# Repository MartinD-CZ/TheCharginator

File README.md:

# The CHARGINATOR
*Upcycle your old ATX power supply into this 11-port QC-compatible charging monstrosity!*

Features:
* connects to an old PC power supply via a 24-pin MOLEX Mini-fit Jr. connector.
* provides power-on switch and LED, stand-by LED and three load resistors.
* 4 USB ports, compatible with QC3.0 (up to 24 W per port, 12 V 2 A), FCP (Huawei), DCP (Apple) and BCP (Battery Charging Protocol).
* 6 USB ports, compatible with DCP and BCP (5 V 2 A per port).
* 1 USB stand-by port, copatible with DCP and BCP (5 V 2 A per port).
* Each output individually fused with resetable fuse.
* Also, screw terminals with 3.3, 5 and 12 V are available.

Links:
* [Hackaday article]()
* [Article on my blog, explaining how the QC part works](http://embedblog.eu/?p=504)
* [FP6601 datasheet](https://datasheet.lcsc.com/szlcsc/Fitipower-Integrated-Tech-FP6601QS6_C86198.pdf)

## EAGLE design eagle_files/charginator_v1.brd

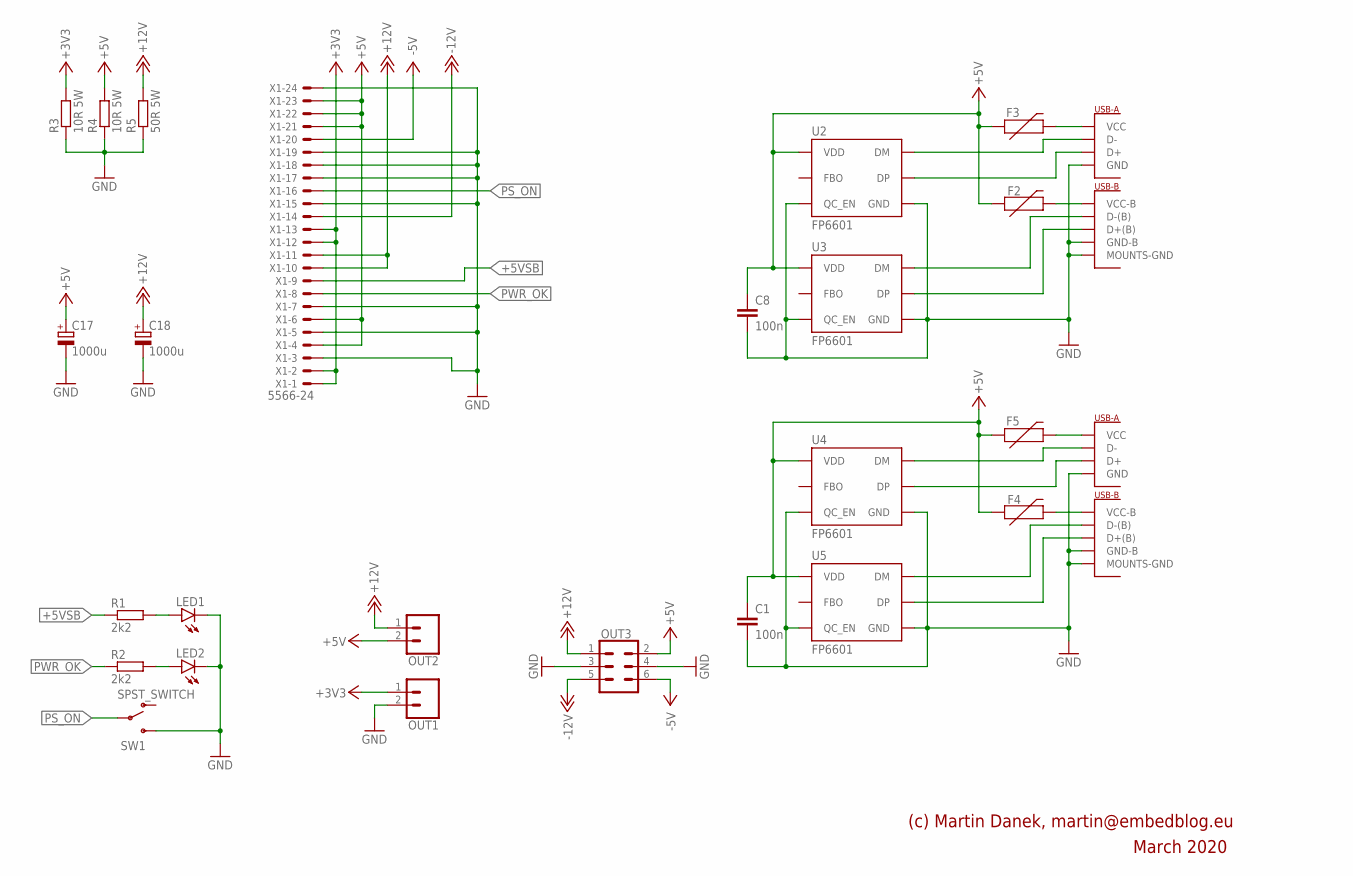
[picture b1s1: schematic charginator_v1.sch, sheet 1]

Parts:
C1, C8: 100n; C1206
C17: 1000u; E5-10,5
C18: 1000u; E5-13
F2, F3, F4, F5: 6V/2A; 1206
LED1, LED2: LED5MM
OUT1, OUT2: 5MM_SCREWTERMINAL_LARGE; SCREWTERMINAL-5MM-2
OUT3: FEMALE 2x3; 2X3
R1, R2: 2k2; M1206
R3, R4: 10R 5W; POWER_RESISTOR_5W
R5: 50R 5W; POWER_RESISTOR_5W
SW1: SPST_SWITCH; TL3XYO
U2, U3, U4, U5: FP6601; SOT23-6
U$1, U$2: DUAL-PORT-USB-REC; DUAL-PORT-USB
X1: 5566-24

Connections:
+3V3: OUT1.1, R3.P$2 (2), X1.1, X1.2, X1.12, X1.13
+5V: C1.1, C8.1, C17.+, F2.1, F3.1, F4.1, F5.1, OUT2.2, OUT3.2, R4.P$2 (2), U2.5 (VDD), U3.5 (VDD), U4.5 (VDD), U5.5 (VDD), X1.4, X1.6, X1.21, X1.22, X1.23; also elsewhere on the board
+5VSB: R1.1, X1.9; also elsewhere on the board
+12V: C18.+, OUT2.1, OUT3.1, R5.P$2 (2), X1.10, X1.11; also elsewhere on the board
-5V: OUT3.6, X1.20
-12V: OUT3.5, X1.14
GND: C1.2, C8.2, C17.-, C18.-, LED1.K (C), LED2.K (C), OUT1.2, OUT3.3, OUT3.4, R3.P$1 (1), R4.P$1 (1), R5.P$1 (1), SW1.1 (S), U2.2 (GND), U2.4 (QC_EN), U3.2 (GND), U3.4 (QC_EN), U4.2 (GND), U4.4 (QC_EN), U5.2 (GND), U5.4 (QC_EN), U$1.GND (MOUNTS-GND), U$1.P$2 (MOUNTS-GND), U$1.P$3 (MOUNTS-GND), U$1.P$4 (MOUNTS-GND), U$1.P$9 (GND-B), U$1.P$11 (GND), U$2.GND (MOUNTS-GND), U$2.P$2 (MOUNTS-GND), U$2.P$3 (MOUNTS-GND), U$2.P$4 (MOUNTS-GND), U$2.P$9 (GND-B), U$2.P$11 (GND), X1.3, X1.5, X1.7, X1.15, X1.17, X1.18, X1.19, X1.24; also elsewhere on the board
unnamed: LED1.A, R1.2
unnamed: LED2.A, R2.2
unnamed: F4.2, U$2.P$10 (VCC-B)
unnamed: F5.2, U$2.P$12 (VCC)
unnamed: F2.2, U$1.P$10 (VCC-B)
unnamed: F3.2, U$1.P$12 (VCC)
unnamed: U2.6 (DM), U$1.P$7 (D-)
unnamed: U2.1 (DP), U$1.P$8 (D+)
unnamed: U4.6 (DM), U$2.P$7 (D-)
unnamed: U4.1 (DP), U$2.P$8 (D+)
unnamed: U5.6 (DM), U$2.P$5 (D-(B))
unnamed: U5.1 (DP), U$2.P$6 (D+(B))
unnamed: U3.6 (DM), U$1.P$5 (D-(B))
unnamed: U3.1 (DP), U$1.P$6 (D+(B))
PS_ON: SW1.2, X1.16
PWR_OK: R2.1, X1.8

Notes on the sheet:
(c) Martin Danek, martin@embedblog.eu
March 2020

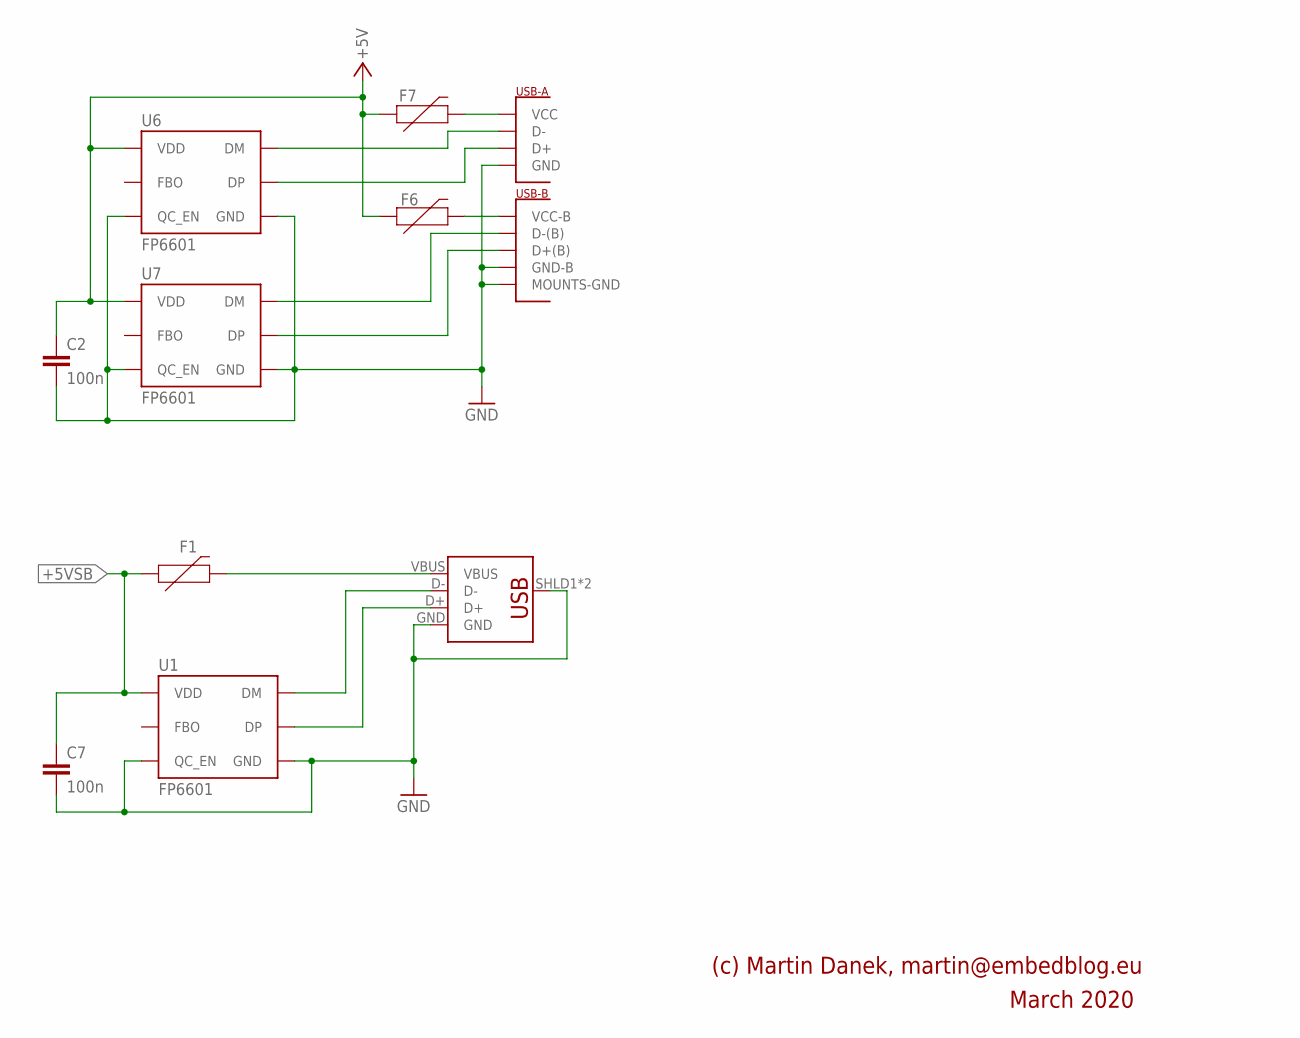
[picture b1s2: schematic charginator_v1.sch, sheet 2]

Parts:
C2, C7: 100n; C1206
F1, F6, F7: 6V/2A; 1206
U1, U6, U7: FP6601; SOT23-6
U$3: DUAL-PORT-USB-REC; DUAL-PORT-USB
U$5: USB_A_REVERSED; USB-A-S-SILK-FEMALE

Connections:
+5V: C2.1, F6.1, F7.1, U6.5 (VDD), U7.5 (VDD); also elsewhere on the board
+5VSB: C7.1, F1.1, U1.5 (VDD); also elsewhere on the board
GND: C2.2, C7.2, U1.2 (GND), U1.4 (QC_EN), U6.2 (GND), U6.4 (QC_EN), U7.2 (GND), U7.4 (QC_EN), U$3.GND (MOUNTS-GND), U$3.P$2 (MOUNTS-GND), U$3.P$3 (MOUNTS-GND), U$3.P$4 (MOUNTS-GND), U$3.P$9 (GND-B), U$3.P$11 (GND), U$5.GND, U$5.SHLD1 (SHIELD), U$5.SHLD2 (SHIELD); also elsewhere on the board
unnamed: F1.2, U$5.VBUS
unnamed: U1.6 (DM), U$5.D-
unnamed: F6.2, U$3.P$10 (VCC-B)
unnamed: U1.1 (DP), U$5.D+
unnamed: F7.2, U$3.P$12 (VCC)
unnamed: U6.6 (DM), U$3.P$7 (D-)
unnamed: U6.1 (DP), U$3.P$8 (D+)
unnamed: U7.6 (DM), U$3.P$5 (D-(B))
unnamed: U7.1 (DP), U$3.P$6 (D+(B))

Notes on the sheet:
(c) Martin Danek, martin@embedblog.eu
March 2020

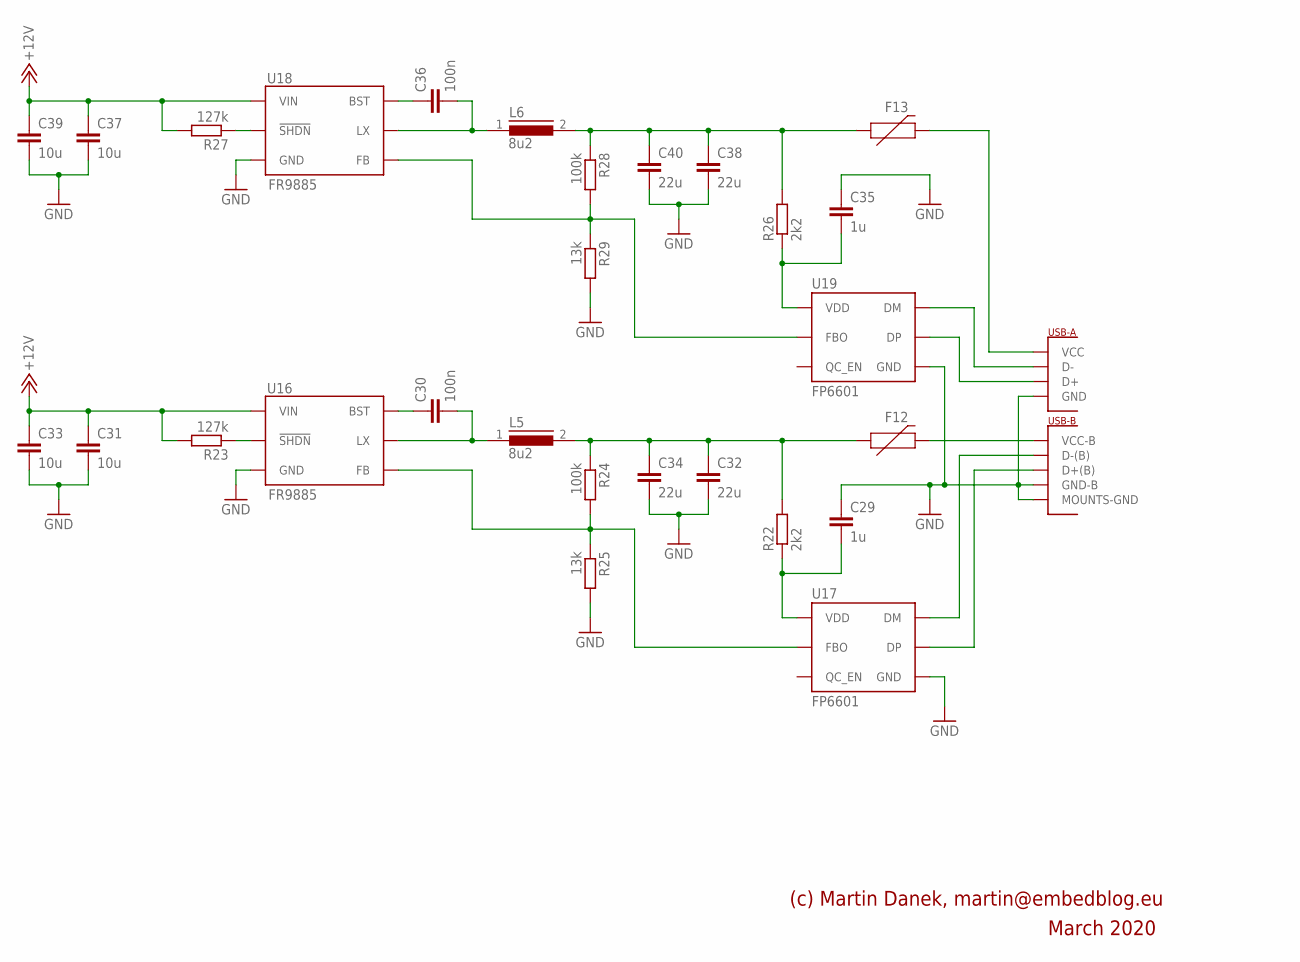
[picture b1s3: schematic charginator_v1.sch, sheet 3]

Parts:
C29, C35: 1u; C1206
C30, C36: 100n; C1206
C31, C33, C37, C39: 10u; C1206
C32, C34, C38, C40: 22u; C1206
F12, F13: 12V/2A; 1206
L5, L6: 8u2; DR73
R22, R26: 2k2; R1206
R23, R27: 127k; R1206
R24, R28: 100k; R1206
R25, R29: 13k; R1206
U16, U18: FR9885; SOT23-6
U17, U19: FP6601; SOT23-6
U$6: DUAL-PORT-USB-REC; DUAL-PORT-USB

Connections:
+12V: C31.1, C33.1, C37.1, C39.1, R23.2, R27.2, U16.5 (VIN), U18.5 (VIN); also elsewhere on the board
FB5: R24.2, R25.1, U16.3 (FB), U17.3 (FBO)
FB6: R28.2, R29.1, U18.3 (FB), U19.3 (FBO)
GND: C29.1, C31.2, C32.2, C33.2, C34.2, C35.1, C37.2, C38.2, C39.2, C40.2, R25.2, R29.2, U16.2 (GND), U17.2 (GND), U18.2 (GND), U19.2 (GND), U$6.GND (MOUNTS-GND), U$6.P$2 (MOUNTS-GND), U$6.P$3 (MOUNTS-GND), U$6.P$4 (MOUNTS-GND), U$6.P$9 (GND-B), U$6.P$11 (GND); also elsewhere on the board
LX5: C30.2, L5.1, U16.6 (LX)
LX6: C36.2, L6.1, U18.6 (LX)
unnamed: C32.1, C34.1, F12.1, L5.2, R22.2, R24.1
unnamed: C29.2, R22.1, U17.5 (VDD)
unnamed: R23.1, U16.4 (!SHDN)
unnamed: C30.1, U16.1 (BST)
unnamed: U17.6 (DM), U$6.P$5 (D-(B))
unnamed: U17.1 (DP), U$6.P$6 (D+(B))
unnamed: C38.1, C40.1, F13.1, L6.2, R26.2, R28.1
unnamed: C35.2, R26.1, U19.5 (VDD)
unnamed: R27.1, U18.4 (!SHDN)
unnamed: C36.1, U18.1 (BST)
unnamed: U19.1 (DP), U$6.P$8 (D+)
unnamed: U19.6 (DM), U$6.P$7 (D-)
unnamed: F13.2, U$6.P$12 (VCC)
VBUS3: F12.2, U$6.P$10 (VCC-B)

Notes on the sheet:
(c) Martin Danek, martin@embedblog.eu
March 2020

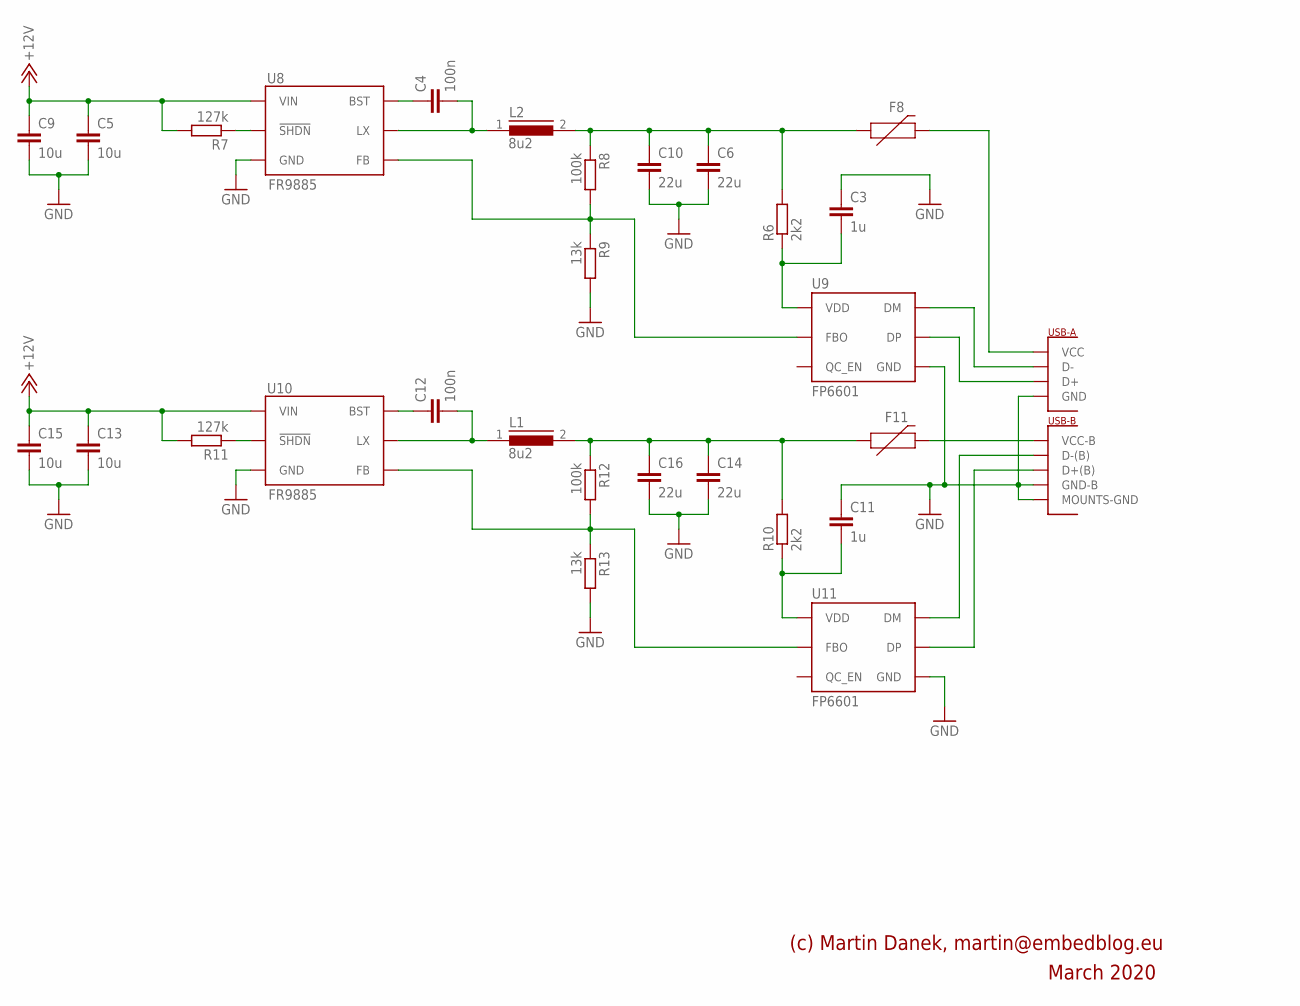
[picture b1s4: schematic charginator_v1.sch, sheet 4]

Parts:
C3, C11: 1u; C1206
C4, C12: 100n; C1206
C5, C9, C13, C15: 10u; C1206
C6, C10, C14, C16: 22u; C1206
F8, F11: 12V/2A; 1206
L1, L2: 8u2; DR73
R6, R10: 2k2; R1206
R7, R11: 127k; R1206
R8, R12: 100k; R1206
R9, R13: 13k; R1206
U8, U10: FR9885; SOT23-6
U9, U11: FP6601; SOT23-6
U$4: DUAL-PORT-USB-REC; DUAL-PORT-USB

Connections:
+12V: C5.1, C9.1, C13.1, C15.1, R7.2, R11.2, U8.5 (VIN), U10.5 (VIN); also elsewhere on the board
FB1: R12.2, R13.1, U10.3 (FB), U11.3 (FBO)
FB2: R8.2, R9.1, U8.3 (FB), U9.3 (FBO)
GND: C3.1, C5.2, C6.2, C9.2, C10.2, C11.1, C13.2, C14.2, C15.2, C16.2, R9.2, R13.2, U8.2 (GND), U9.2 (GND), U10.2 (GND), U11.2 (GND), U$4.GND (MOUNTS-GND), U$4.P$2 (MOUNTS-GND), U$4.P$3 (MOUNTS-GND), U$4.P$4 (MOUNTS-GND), U$4.P$9 (GND-B), U$4.P$11 (GND); also elsewhere on the board
LX1: C12.2, L1.1, U10.6 (LX)
LX2: C4.2, L2.1, U8.6 (LX)
unnamed: C6.1, C10.1, F8.1, L2.2, R6.2, R8.1
unnamed: C3.2, R6.1, U9.5 (VDD)
unnamed: R7.1, U8.4 (!SHDN)
unnamed: C4.1, U8.1 (BST)
unnamed: U9.1 (DP), U$4.P$8 (D+)
unnamed: U9.6 (DM), U$4.P$7 (D-)
unnamed: F8.2, U$4.P$12 (VCC)
unnamed: C14.1, C16.1, F11.1, L1.2, R10.2, R12.1
unnamed: C11.2, R10.1, U11.5 (VDD)
unnamed: R11.1, U10.4 (!SHDN)
unnamed: C12.1, U10.1 (BST)
unnamed: U11.6 (DM), U$4.P$5 (D-(B))
unnamed: U11.1 (DP), U$4.P$6 (D+(B))
VBUS1: F11.2, U$4.P$10 (VCC-B)

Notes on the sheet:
(c) Martin Danek, martin@embedblog.eu
March 2020

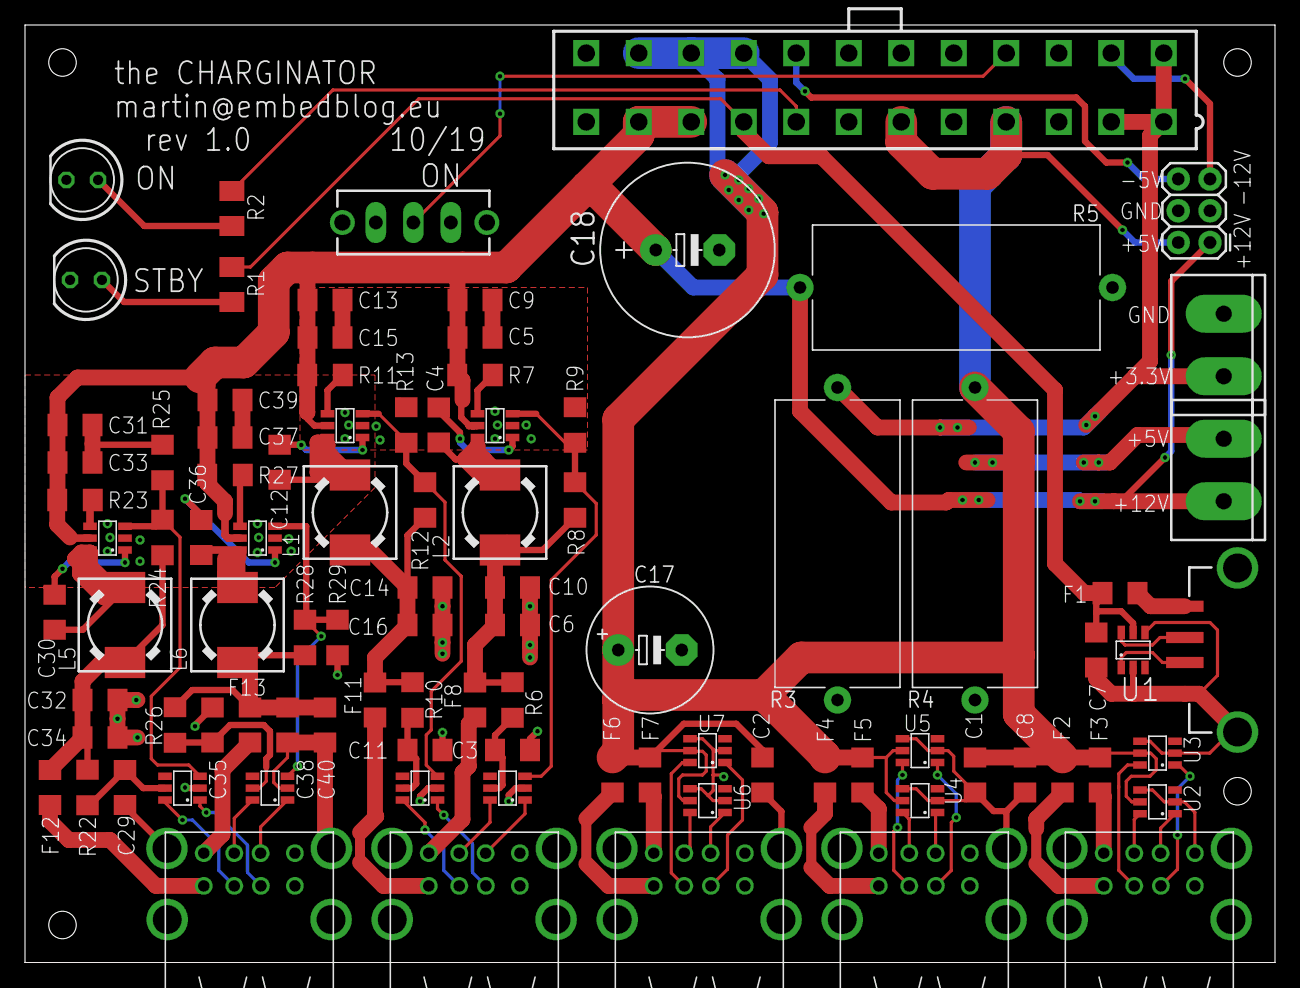
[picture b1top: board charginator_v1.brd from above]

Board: 2 copper layers, 100.0 x 75.0 mm, 94 parts (0 on the bottom side), 68 nets.

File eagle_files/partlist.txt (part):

Partlist

Exported from charginator_v1.sch at 01.04.2020 11:05

EAGLE Version 9.3.0 Copyright (c) 1988-2019 Autodesk, Inc.

Assembly variant: 

Part     Value                   Device                  Package             Library             Sheet

C1       100n                    C-EUC1206               C1206               resistor            1
C2       100n                    C-EUC1206               C1206               resistor            2
C3       1u                      C-EUC1206               C1206               resistor            4
C4       100n                    C-EUC1206               C1206               resistor            4
C5       10u                     C-EUC1206               C1206               resistor            4
C6       22u                     C-EUC1206               C1206               resistor            4
C7       100n                    C-EUC1206               C1206               resistor            2
C8       100n                    C-EUC1206               C1206               resistor            1
C9       10u                     C-EUC1206               C1206               resistor            4
C10      22u                     C-EUC1206               C1206               resistor            4
C11      1u                      C-EUC1206               C1206               resistor            4
C12      100n                    C-EUC1206               C1206               resistor            4
C13      10u                     C-EUC1206               C1206               resistor            4
C14      22u                     C-EUC1206               C1206               resistor            4
C15      10u                     C-EUC1206               C1206               resistor            4
C16      22u                     C-EUC1206               C1206               resistor            4
C17      1000u                   CPOL-EUE5-10.5          E5-10,5             resistor            1
C18      1000u                   CPOL-EUE5-13            E5-13               resistor            1
C29      1u                      C-EUC1206               C1206               resistor            3
C30      100n                    C-EUC1206               C1206               resistor            3
C31      10u                     C-EUC1206               C1206               resistor            3
C32      22u                     C-EUC1206               C1206               resistor            3
C33      10u                     C-EUC1206               C1206               resistor            3
C34      22u                     C-EUC1206               C1206               resistor            3
C35      1u                      C-EUC1206               C1206               resistor            3
C36      100n                    C-EUC1206               C1206               resistor            3
C37      10u                     C-EUC1206               C1206               resistor            3
C38      22u                     C-EUC1206               C1206               resistor            3
C39      10u                     C-EUC1206               C1206               resistor            3
C40      22u                     C-EUC1206               C1206               resistor            3
F1       6V/2A                   PPTC_HALF-AMP           1206                SparkFun-Fuses      2
F2       6V/2A                   PPTC_HALF-AMP           1206                SparkFun-Fuses      1
F3       6V/2A                   PPTC_HALF-AMP           1206                SparkFun-Fuses      1
F4       6V/2A                   PPTC_HALF-AMP           1206                SparkFun-Fuses      1
F5       6V/2A                   PPTC_HALF-AMP           1206                SparkFun-Fuses      1
F6       6V/2A                   PPTC_HALF-AMP           1206                SparkFun-Fuses      2
F7       6V/2A                   PPTC_HALF-AMP           1206                SparkFun-Fuses      2
F8       12V/2A                  PPTC_HALF-AMP           1206                SparkFun-Fuses      4
F11      12V/2A                  PPTC_HALF-AMP           1206                SparkFun-Fuses      4
F12      12V/2A                  PPTC_HALF-AMP           1206                SparkFun-Fuses      3
F13      12V/2A                  PPTC_HALF-AMP           1206                SparkFun-Fuses      3
L1       8u2                     DR73                    DR73                inductors           4
L2       8u2                     DR73                    DR73                inductors           4
L5       8u2                     DR73                    DR73                inductors           3
L6       8u2                     DR73                    DR73                inductors           3
LED1                             LED5MM                  LED5MM              led                 1
LED2                             LED5MM                  LED5MM              led                 1
OUT1     5MM_SCREWTERMINAL_LARGE 5MM_SCREWTERMINAL_LARGE SCREWTERMINAL-5MM-2 custom              1
OUT2     5MM_SCREWTERMINAL_LARGE 5MM_SCREWTERMINAL_LARGE SCREWTERMINAL-5MM-2 custom              1
OUT3     FEMALE 2x3              CONN_03X2FEMALE         2X3                 SparkFun-Connectors 1
R1       2k2                     R-EU_M1206              M1206               resistor            1
R2       2k2                     R-EU_M1206              M1206               resistor            1
R3       10R 5W                  RESISTOR_5W             POWER_RESISTOR_5W   custom              1
R4       10R 5W                  RESISTOR_5W             POWER_RESISTOR_5W   custom              1
R5       50R 5W                  RESISTOR_5W             POWER_RESISTOR_5W   custom              1
R6       2k2                     R-EU_R1206              R1206               resistor            4
R7       127k                    R-EU_R1206              R1206               resistor            4
R8       100k                    R-EU_R1206              R1206               resistor            4
R9       13k                     R-EU_R1206              R1206               resistor            4
R10      2k2                     R-EU_R1206              R1206               resistor            4
R11      127k                    R-EU_R1206              R1206               resistor            4
R12      100k                    R-EU_R1206              R1206               resistor            4
R13      13k                     R-EU_R1206              R1206               resistor            4
R22      2k2                     R-EU_R1206              R1206               resistor            3
R23      127k                    R-EU_R1206              R1206               resistor            3
R24      100k                    R-EU_R1206              R1206               resistor            3
R25      13k                     R-EU_R1206              R1206               resistor            3
R26      2k2                     R-EU_R1206              R1206               resistor            3
R27      127k                    R-EU_R1206              R1206               resistor            3
R28      100k                    R-EU_R1206              R1206               resistor            3
R29      13k                     R-EU_R1206              R1206               resistor            3
SW1      SPST_SWITCH             SPST_SWITCH             TL3XYO              custom              1
U$1      DUAL-PORT-USB-REC       DUAL-PORT-USB-REC       DUAL-PORT-USB       tps2511             1
U$2      DUAL-PORT-USB-REC       DUAL-PORT-USB-REC       DUAL-PORT-USB       tps2511             1
U$3      DUAL-PORT-USB-REC       DUAL-PORT-USB-REC       DUAL-PORT-USB       tps2511             2
U$4      DUAL-PORT-USB-REC       DUAL-PORT-USB-REC       DUAL-PORT-USB       tps2511             4
U$5      USB_A_REVERSED          USB_A_REVERSED          USB-A-S-SILK-FEMALE custom              2
U$6      DUAL-PORT-USB-REC       DUAL-PORT-USB-REC       DUAL-PORT-USB       tps2511             3
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
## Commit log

2020-04-01 initial release
    ---

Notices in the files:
parts and their libraries:
SparkFun-Fuses: Licensing: Creative Commons ShareAlike 4.0 International - https://creativecommons.org/licenses/by-sa/4.0
